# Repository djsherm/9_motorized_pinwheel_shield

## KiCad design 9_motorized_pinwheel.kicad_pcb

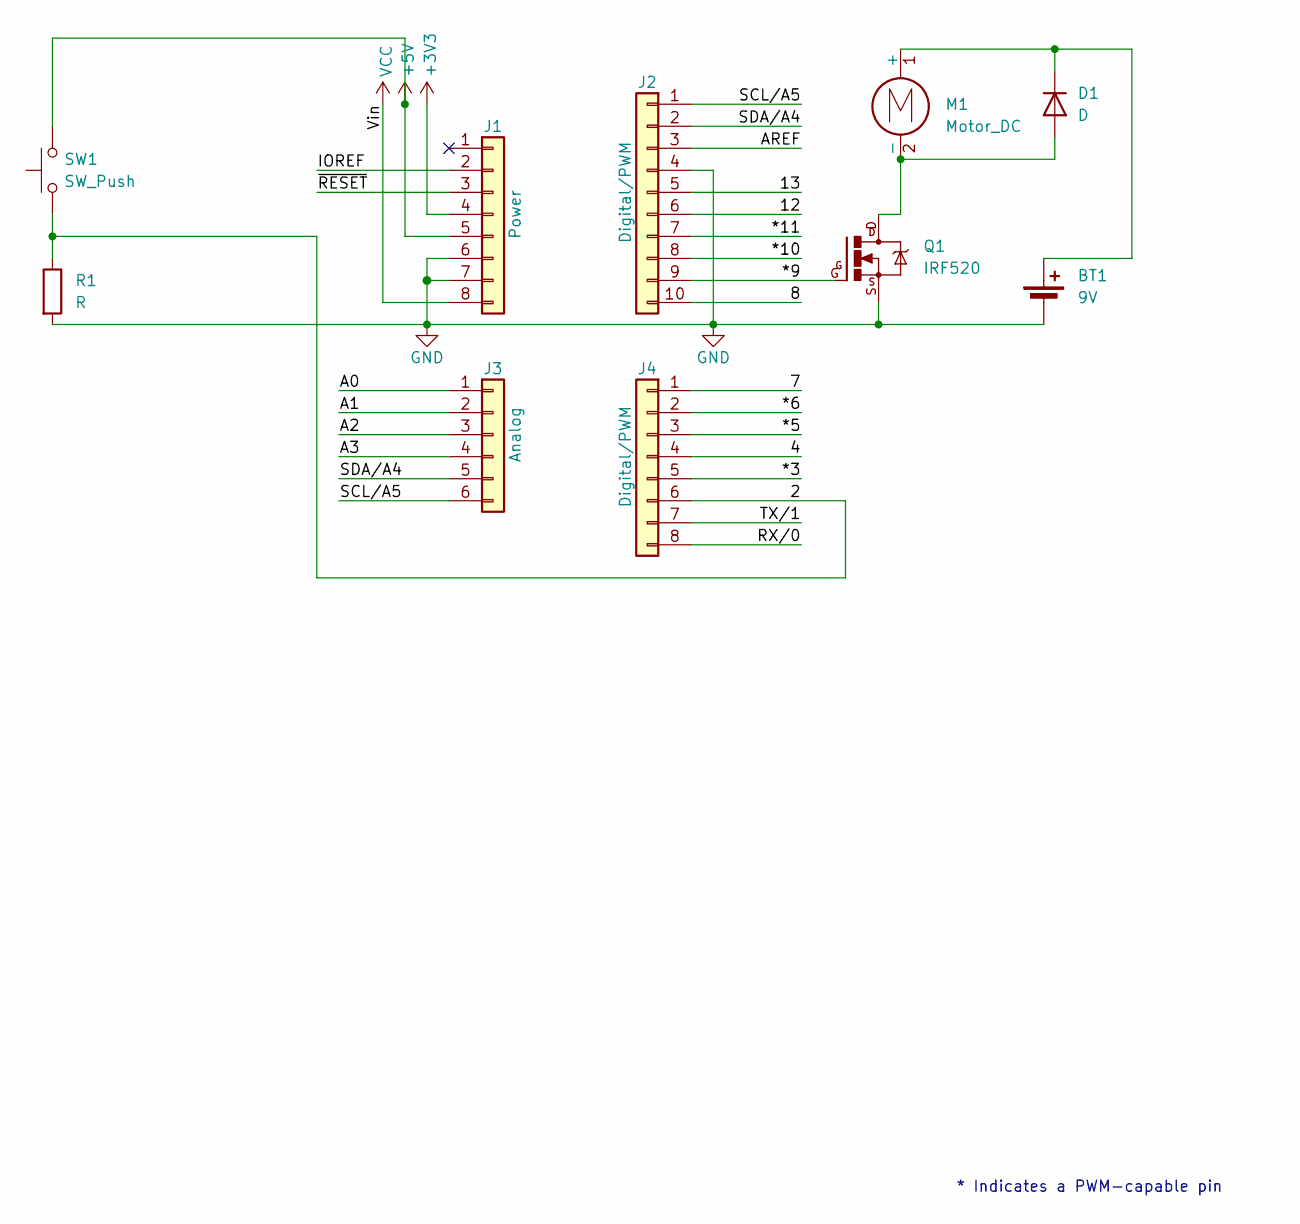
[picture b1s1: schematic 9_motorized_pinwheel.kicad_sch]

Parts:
BT1: 9V; PinHeader_1x02_P2.54mm_Vertical
D1: D; D_A-405_P7.62mm_Horizontal
J1: Power; PinSocket_1x08_P2.54mm_Vertical
J2: Digital/PWM; PinSocket_1x10_P2.54mm_Vertical
J3: Analog; PinSocket_1x06_P2.54mm_Vertical
J4: Digital/PWM; PinSocket_1x08_P2.54mm_Vertical
M1: Motor_DC; PinHeader_1x02_P2.54mm_Vertical
Q1: IRF520; TO220BV
R1: R; R_Axial_DIN0207_L6.3mm_D2.5mm_P10.16mm_Horizontal
SW1: SW_Push; TS02 push button

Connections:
+3V3: J1.4
+5V: J1.5, SW1.2
/2: J4.6, R1.1, SW1.1
/4: J4.4
/7: J4.1
/8: J2.10
/12: J2.6
/13: J2.5
/*3: J4.5
/*5: J4.3
/*6: J4.2
/*9: J2.9, Q1.G
/*10: J2.8
/*11: J2.7
/A0: J3.1
/A1: J3.2
/A2: J3.3
/A3: J3.4
/AREF: J2.3
/IOREF: J1.2
/RX/0: J4.8
/SCL/A5: J2.1, J3.6
/SDA/A4: J2.2, J3.5
/TX/1: J4.7
/~RESET: J1.3
GND: BT1.2 (-), J1.6, J1.7, J2.4, Q1.S, R1.2
unnamed: BT1.1 (+), D1.1 (K), M1.1 (+)
unnamed: D1.2 (A), M1.2 (-), Q1.D
VCC: J1.8

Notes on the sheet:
* Indicates a PWM-capable pin

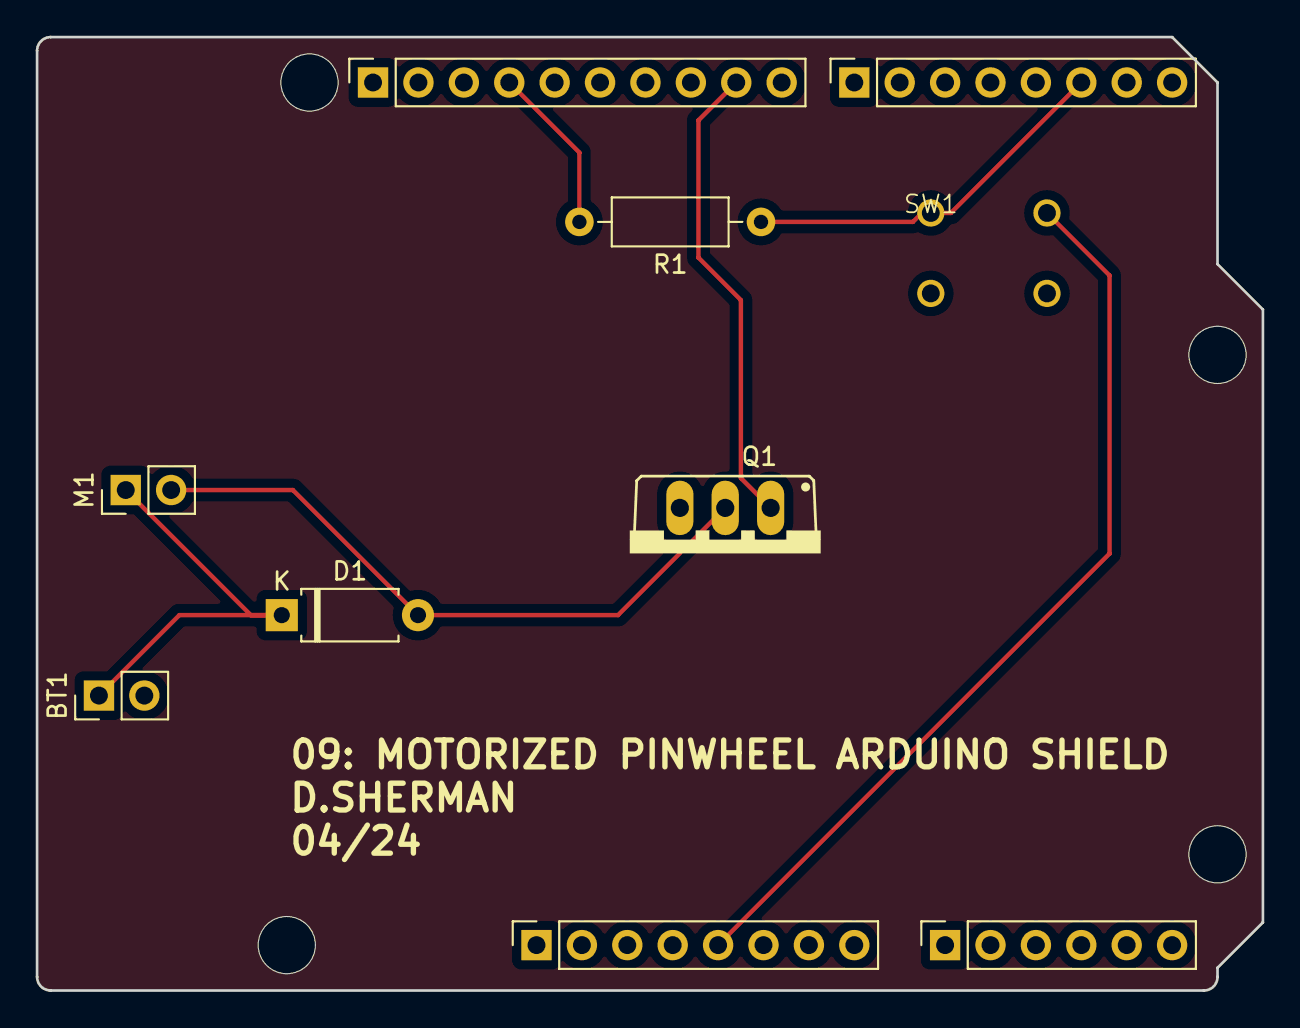
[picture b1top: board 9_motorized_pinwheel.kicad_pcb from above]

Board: 2 copper layers, 68.6 x 53.3 mm, 14 parts (0 on the bottom side), 8 nets.

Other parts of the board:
MH1, MH2, MH3, MH4: MountingHole_3.2mm
